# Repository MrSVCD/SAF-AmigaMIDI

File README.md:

# SAF-AmigaMIDI

## Not verified

A somewhat faithful recreation of the Amiga MIDI interface from
"ST Amiga Format" issue 5

In the folder [CNC-version/](CNC-version/) is a mainly single sided design that
is targeting toner transfer, home photolithography and CNC milling. There are a
place for a optional L7805 voltage regulator. There are only two jumper wires in
this design that is shown as upper PCB layer.

Original article [Documents/SAF-AmigaMIDI.pdf](Documents/SAF-AmigaMIDI.pdf)

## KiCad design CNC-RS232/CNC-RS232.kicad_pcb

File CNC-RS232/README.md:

# SAF-AmigaMIDI-CNC

This version is also for making the midi interface at home but also at a PCB house.

It is dual sided but the top layer can be replaced with two jumper wires.
The RS232 send interface is improved to provide a negative voltage that are not
strictly nessesary for the serial port on a Amiga.
There are also a optional voltage regulator spot.

It is made to fit on a 100✕80mm, Half a Eurocard.

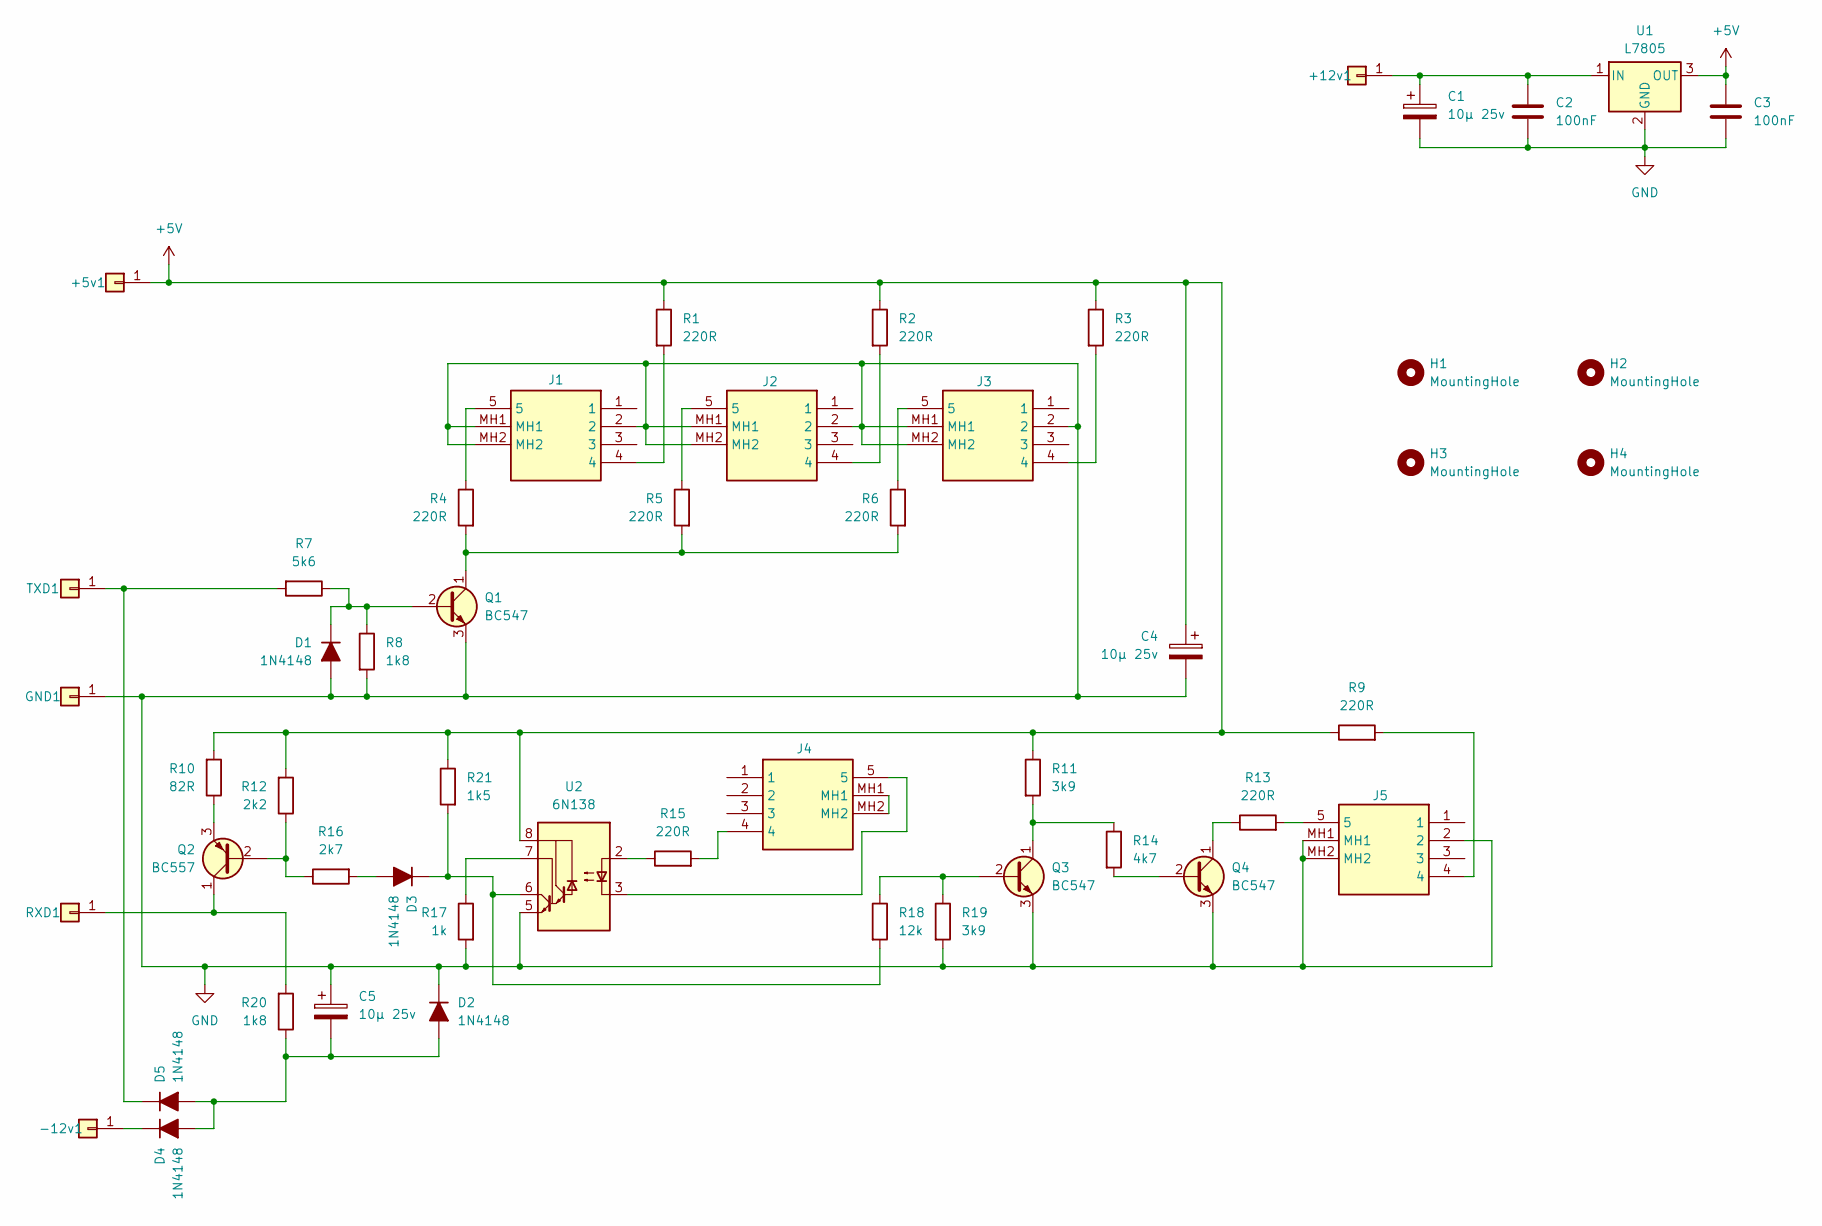
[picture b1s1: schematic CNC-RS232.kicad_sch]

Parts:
+5v1, +12v1: Conn_01x01; SolderWire-1.5sqmm_1x01_D1.7mm_OD3.9mm
-12v1: Conn_01x01; SolderWire-1.5sqmm_1x01_D1.7mm_OD3.9mm
C1, C4, C5: 10µ 25v; CP_Radial_D5.0mm_P2.00mm
C2, C3: 100nF; C_Rect_L4.0mm_W2.5mm_P2.50mm
D1, D2, D3, D4, D5: 1N4148; D_DO-35_SOD27_P10.16mm_Horizontal
GND1: Conn_01x01; SolderWire-1.5sqmm_1x01_D1.7mm_OD3.9mm
H1, H2, H3, H4: MountingHole; MountingHole_3.2mm_M3
J1, J2, J3: DIN-5_180degree; KCDX5SN; Mouser Part Number 806-KCDX-5S-N
J4, J5: DIN-5_180degree; KCDX5SN
Q1, Q3, Q4: BC547; TO-92_Inline_Wide_CBE
Q2: BC557; TO-92_Inline_Wide
R1, R2, R3, R4, R5, R6, R9, R13, R15: 220R; R_Axial_DIN0207_L6.3mm_D2.5mm_P10.16mm_Horizontal
R7: 5k6; R_Axial_DIN0207_L6.3mm_D2.5mm_P10.16mm_Horizontal
R8, R20: 1k8; R_Axial_DIN0207_L6.3mm_D2.5mm_P10.16mm_Horizontal
R10: 82R; R_Axial_DIN0207_L6.3mm_D2.5mm_P10.16mm_Horizontal
R11, R19: 3k9; R_Axial_DIN0207_L6.3mm_D2.5mm_P10.16mm_Horizontal
R12: 2k2; R_Axial_DIN0207_L6.3mm_D2.5mm_P10.16mm_Horizontal
R14: 4k7; R_Axial_DIN0207_L6.3mm_D2.5mm_P10.16mm_Horizontal
R16: 2k7; R_Axial_DIN0207_L6.3mm_D2.5mm_P10.16mm_Horizontal
R17: 1k; R_Axial_DIN0207_L6.3mm_D2.5mm_P10.16mm_Horizontal
R18: 12k; R_Axial_DIN0207_L6.3mm_D2.5mm_P10.16mm_Horizontal
R21: 1k5; R_Axial_DIN0207_L6.3mm_D2.5mm_P10.16mm_Horizontal
RXD1: Conn_01x01; SolderWire-1.5sqmm_1x01_D1.7mm_OD3.9mm
TXD1: Conn_01x01; SolderWire-1.5sqmm_1x01_D1.7mm_OD3.9mm
U1: L7805; TO-220-3_Vertical
U2: 6N138; DIP-8_W7.62mm_Socket

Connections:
+5V: +5v1.1, C3.1, C4.1, R1.1, R2.1, R3.1, R9.1, R10.2, R11.1, R12.2, R21.1, U1.3 (OUT), U2.8 (VCC)
GND: C1.2, C2.2, C3.2, C4.2, C5.1, D1.2 (A), D2.1 (K), GND1.1, J1.2, J1.MH1, J1.MH2, J2.2, J2.MH1, J2.MH2, J3.2, J3.MH1, J3.MH2, J5.2, J5.MH1, J5.MH2, Q1.3 (E), Q3.3 (E), Q4.3 (E), R8.2, R17.2, R19.2, U1.2 (GND), U2.5 (GND)
unnamed: +12v1.1, C1.1, C2.1, U1.1 (IN)
unnamed: -12v1.1, D4.1 (K)
unnamed: D1.1 (K), Q1.2 (B), R7.1, R8.1
unnamed: C5.2, D2.2 (A), D4.2 (A), D5.2 (A), R20.1
unnamed: D3.2 (A), R16.2
unnamed: D3.1 (K), R18.2, R21.2, U2.6 (VO2)
unnamed: D5.1 (K), R7.2, TXD1.1
unnamed: J1.4, R1.2
unnamed: J1.5, R4.1
unnamed: J2.4, R2.2
unnamed: J2.5, R5.1
unnamed: J3.4, R3.2
unnamed: J3.5, R6.1
unnamed: J4.4, R15.2
unnamed: J4.MH1, J4.MH2
unnamed: J5.4, R9.2
unnamed: J5.5, R13.2
unnamed: Q1.1 (C), R4.2, R5.2, R6.2
unnamed: Q2.2 (B), R12.1, R16.1
unnamed: Q2.1 (C), R20.2, RXD1.1
unnamed: Q2.3 (E), R10.1
unnamed: Q3.2 (B), R18.1, R19.1
unnamed: Q3.1 (C), R11.2, R14.1
unnamed: Q4.2 (B), R14.2
unnamed: Q4.1 (C), R13.1
unnamed: R15.1, U2.2 (C1)
unnamed: J4.5, U2.3 (C2)
unnamed: R17.1, U2.7 (VO1)

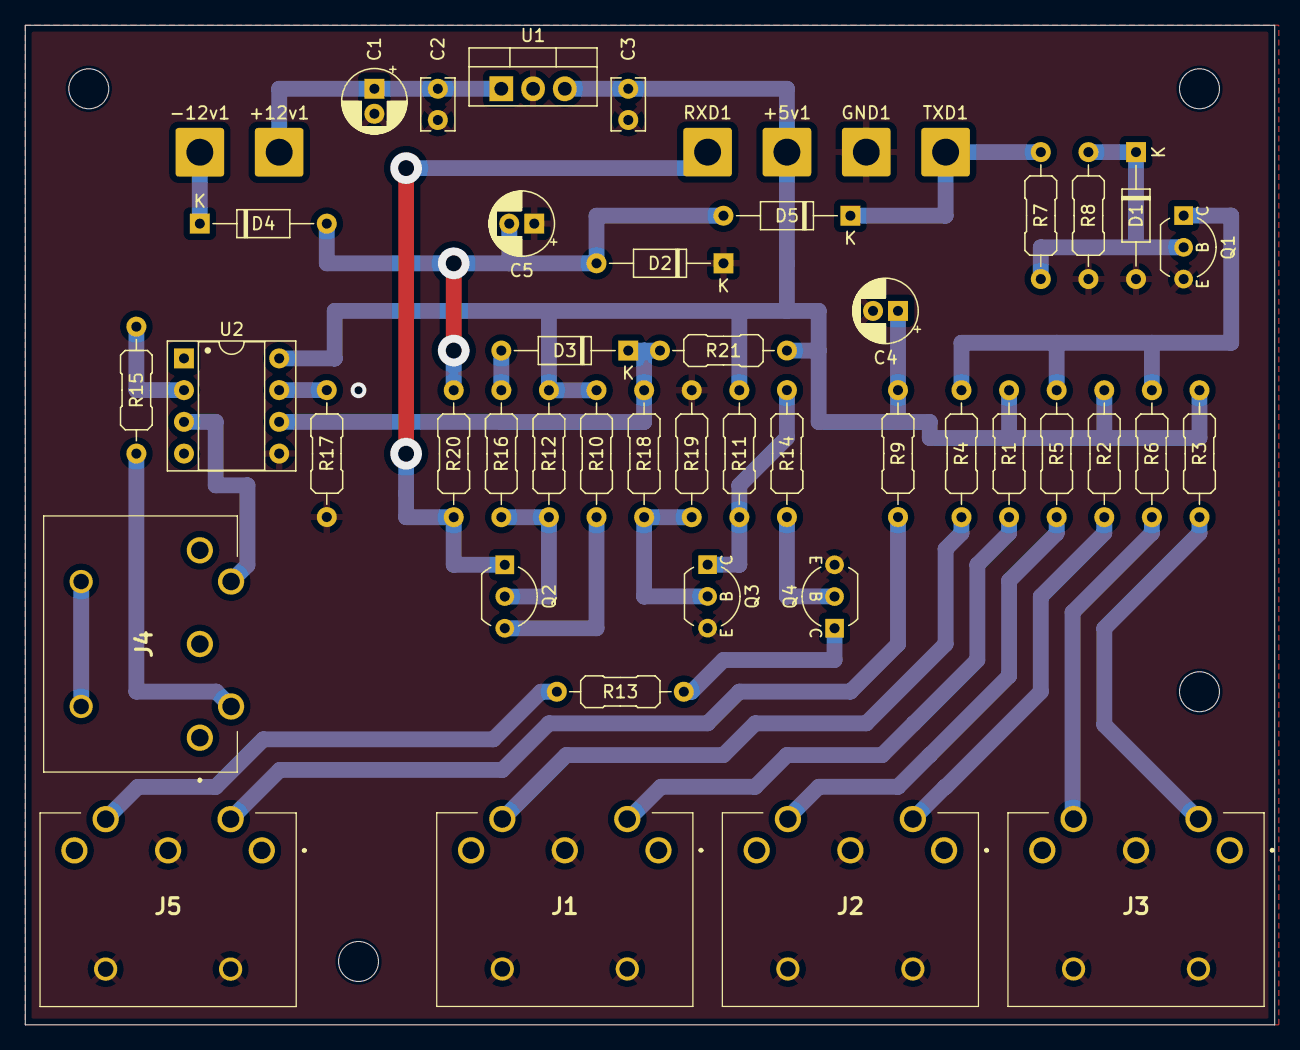
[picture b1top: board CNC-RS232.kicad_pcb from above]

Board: 2 copper layers, 100.0 x 80.0 mm, 52 parts (0 on the bottom side), 30 nets.

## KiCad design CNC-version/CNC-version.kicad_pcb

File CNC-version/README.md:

# SAF-AmigaMIDI-CNC

This version is for making the midi interface at home.

It is single sided with two jumper wires (the wires is shown as the top copper
layer) there are also a optional voltage regulator spot.

It is also made to fit on a 100✕80mm, Half a Eurocard.

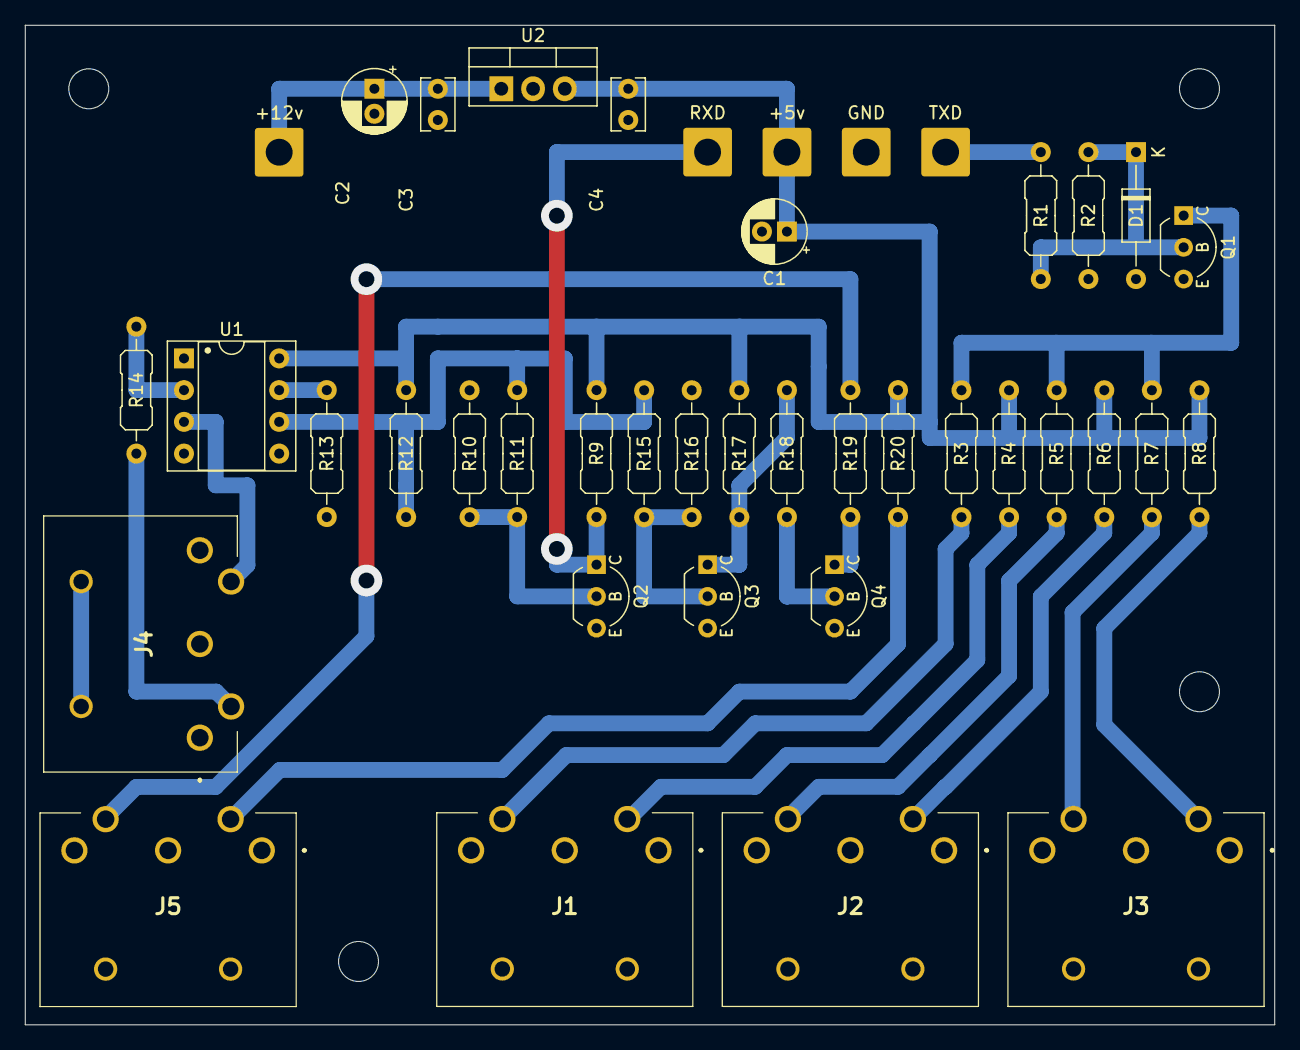
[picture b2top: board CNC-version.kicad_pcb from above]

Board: 2 copper layers, 100.0 x 80.0 mm, 45 parts (0 on the bottom side), 26 nets.

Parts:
+5v, +12v: Conn_01x01; SolderWire-1.5sqmm_1x01_D1.7mm_OD3.9mm
C1, C2: 10µ 25v; CP_Radial_D5.0mm_P2.00mm
C3, C4: 100nF; C_Rect_L4.0mm_W2.5mm_P2.50mm
D1: 1N4148; D_DO-35_SOD27_P10.16mm_Horizontal
GND: Conn_01x01; SolderWire-1.5sqmm_1x01_D1.7mm_OD3.9mm
H1, H2, H3, H4: MountingHole; MountingHole_3.2mm_M3
J1, J2, J3, J4, J5: DIN-5_180degree; KCDX5SN
Q1, Q2, Q3, Q4: BC547; TO-92_Inline_Wide_CBE
R1, R11: 5k6; R_Axial_DIN0207_L6.3mm_D2.5mm_P10.16mm_Horizontal
R2: 1k8; R_Axial_DIN0207_L6.3mm_D2.5mm_P10.16mm_Horizontal
R3, R4, R5, R6, R7, R8, R14, R19, R20: 220R; R_Axial_DIN0207_L6.3mm_D2.5mm_P10.16mm_Horizontal
R9, R13: 1k; R_Axial_DIN0207_L6.3mm_D2.5mm_P10.16mm_Horizontal
R10, R12: 1k5; R_Axial_DIN0207_L6.3mm_D2.5mm_P10.16mm_Horizontal
R15: 12k; R_Axial_DIN0207_L6.3mm_D2.5mm_P10.16mm_Horizontal
R16, R17: 3k9; R_Axial_DIN0207_L6.3mm_D2.5mm_P10.16mm_Horizontal
R18: 4k7; R_Axial_DIN0207_L6.3mm_D2.5mm_P10.16mm_Horizontal
RXD: Conn_01x01; SolderWire-1.5sqmm_1x01_D1.7mm_OD3.9mm
TXD: Conn_01x01; SolderWire-1.5sqmm_1x01_D1.7mm_OD3.9mm
U1: 6N138; DIP-8_W7.62mm_Socket
U2: L7805; TO-220-3_Vertical

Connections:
+5V: +5v.1, C1.1, C4.1, R4.1, R6.1, R8.1, R9.1, R12.2, R17.1, R20.1, U1.8 (VCC), U2.3 (OUT)
GND: C1.2, C2.2, C3.2, C4.2, D1.2 (A), GND.1, J1.2, J1.MH1, J1.MH2, J2.2, J2.MH1, J2.MH2, J3.2, J3.MH1, J3.MH2, J5.2, J5.MH1, J5.MH2, Q1.3 (E), Q2.3 (E), Q3.3 (E), Q4.3 (E), R2.2, R10.2, R13.2, R16.2, U1.5 (GND), U2.2 (GND)
unnamed: +12v.1, C2.1, C3.1, U2.1 (IN)
unnamed: D1.1 (K), Q1.2 (B), R1.1, R2.1
unnamed: J1.4, R4.2
unnamed: J1.5, R3.1
unnamed: J2.4, R6.2
unnamed: J2.5, R5.1
unnamed: J3.4, R8.2
unnamed: J3.5, R7.1
unnamed: J4.4, R14.2
unnamed: J4.MH1, J4.MH2
unnamed: J5.4, R20.2
unnamed: J5.5, R19.2
unnamed: Q1.1 (C), R3.2, R5.2, R7.2
unnamed: Q2.2 (B), R10.1, R11.1
unnamed: Q2.1 (C), R9.2, RXD.1
unnamed: Q3.2 (B), R15.1, R16.1
unnamed: Q3.1 (C), R17.2, R18.1
unnamed: Q4.2 (B), R18.2
unnamed: Q4.1 (C), R19.1
unnamed: R1.2, TXD.1
unnamed: R14.1, U1.2 (C1)
unnamed: J4.5, U1.3 (C2)
unnamed: R13.1, U1.7 (VO1)
unnamed: R11.2, R12.1, R15.2, U1.6 (VO2)

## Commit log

2025-05-03 First CNC version
2025-05-03 Updated Documents and Readme
2025-05-03 Updated Documents
2025-05-03 Update of CNC-version
2025-05-03 Getting there
2025-05-04 Too close for comfort
2025-05-04 Even better layout
2025-05-10 Clean Up
2025-05-10 PCB house branch made
2025-05-10 PCB-house done
2025-05-10 fixed RS232 and Thru
2025-05-10 Cleanup
2025-05-10 PCB cleanup
